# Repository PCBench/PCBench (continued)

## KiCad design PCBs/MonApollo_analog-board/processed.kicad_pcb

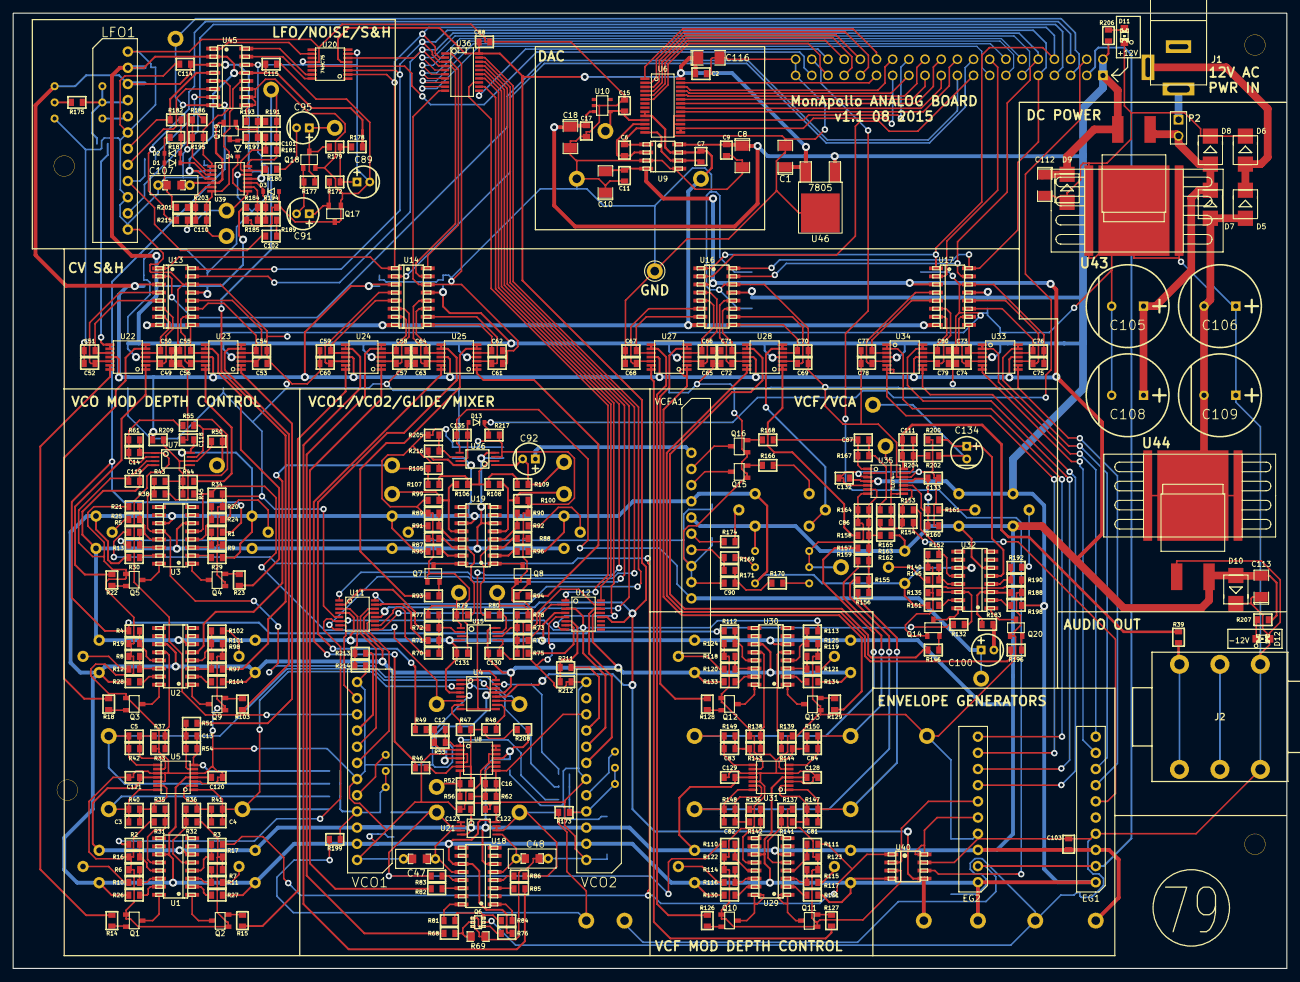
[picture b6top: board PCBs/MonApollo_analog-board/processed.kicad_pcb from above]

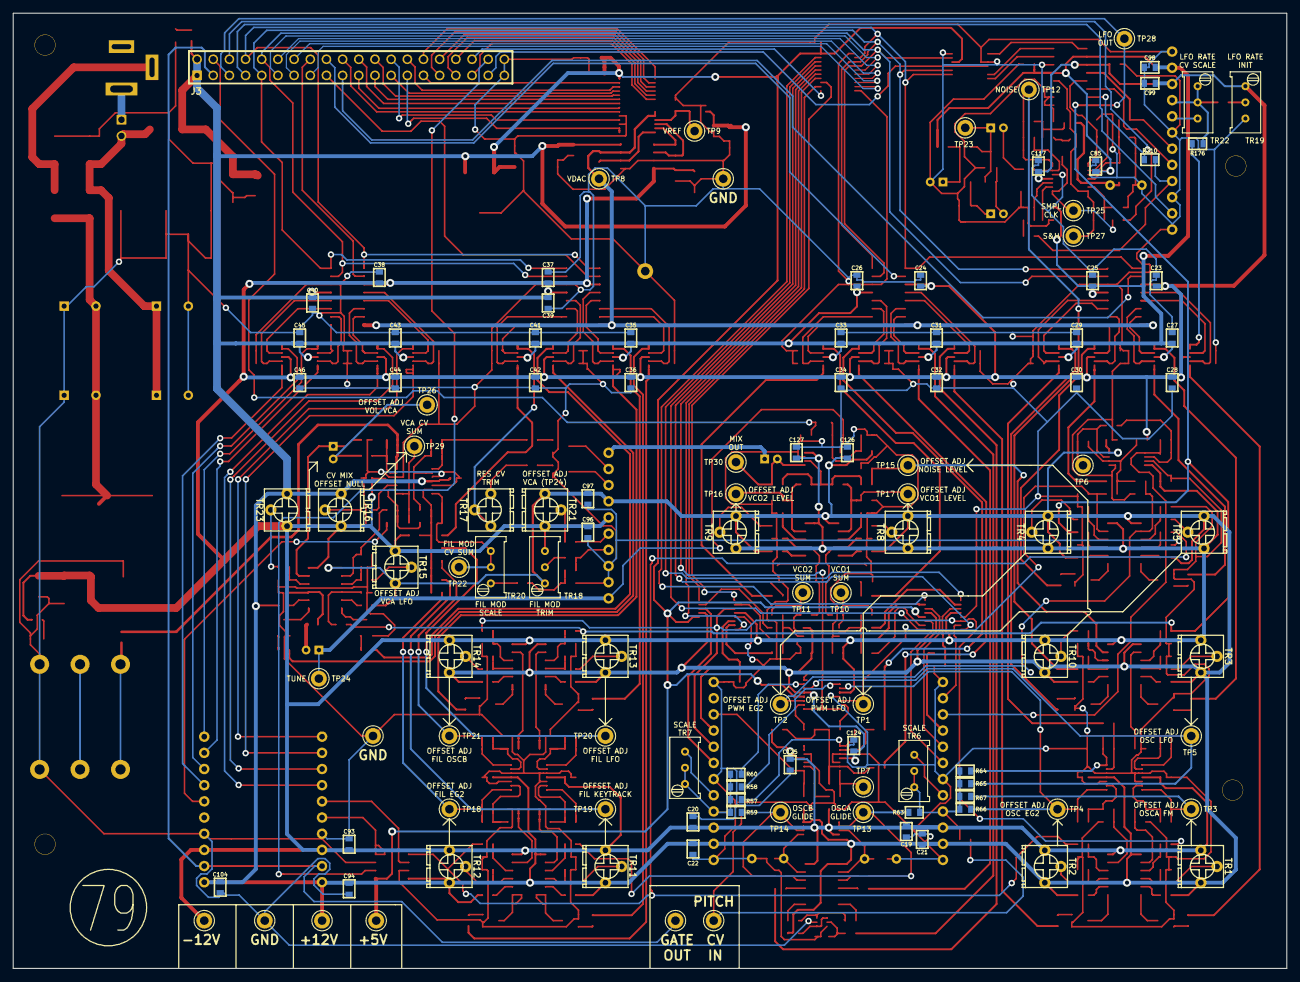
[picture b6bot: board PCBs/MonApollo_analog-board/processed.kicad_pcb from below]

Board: 2 copper layers, 200.0 x 150.0 mm, 506 parts (115 on the bottom side), 352 nets.

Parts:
C1, C8, C10, C18: 1µ; SMD-1206_Pol
C2, C9, C11, C15, C17, C23, C24, C25, C26, C27, C28, C29, C30, C31, C32, C33, C34, C35, C36, C37, C38, C39, C40, C41, C42, C43, C44, C45, C46, C85, C88, C114, C115, C117, C118, C119, C120, C121, C122, C123, C124, C125, C126, C127, C128, C129, C130, C131, C132, C133: 0.1µ; SM0603-C-JRL
C3, C4, C5, C12, C13, C14, C16, C81, C82, C83, C84, C86, C87, C101, C135: 10p; SM0603-C-JRL
C6, C7: 5.6p; SM0603-C-JRL
C19, C20, C21, C22, C93, C94, C96, C97, C98, C99, C103, C104: 1µ; SM0603-C-JRL
C47, C48: 470n; CAP-5MM-BOX-0805-COMBO
C49, C50, C51, C52, C53, C54, C55, C56, C57, C58, C59, C60, C61, C62, C63, C64, C65, C66, C67, C68, C69, C70, C71, C72, C73, C74, C75, C76, C77, C78, C79, C80: 0.01µ; SM0603-C-JRL
C89, C91: 47μ; 2MM-POL-CAP
C90: 100n; SM0603-C-JRL
C92: 1µ; 2MM-POL-CAP
C95: 10μ; 2MM-POL-CAP
C100, C134: 22µ; 2MM-POL-CAP
C102: 4.7n; SM0603-C-JRL
C105, C106, C108, C109: 1000µ; 5MM-POL-CAP
C107: 100n; CAP-5MM-BOX-0805-COMBO
C110: 1.5n; SM0603-C-JRL
C111: 100pF; SM0603-C-JRL
C112, C113, C116: 2.2µ; SMD-1206_Pol
D1, D2, D3, D4: DIODE; SOD323-JRL
D5, D6, D7, D8, D9, D10: DIODE; SMB
D11, D12: LED; LED-0805-JRL
D13: 1N4148; SOD323-JRL
EG1, EG2: EG
HOLE-0.125-INCH, HOLE-0.125-INCH_2, HOLE-0.125-INCH_3, HOLE-0.125-INCH_4: VAL**; HOLE-0.125-INCH
J1: AC IN; 2.1-MM-DC-EJ508A
J2: OUT; JACK_6.35_STEREO_TAYDA
J3: CONN_20X2; PIN_ARRAY_20X2
LFO1: VCO; VCO-SIP
P2: CONN_01X02; PIN_ARRAY_2X1
Q1, Q2, Q3, Q4, Q5, Q7, Q8, Q9, Q10, Q11, Q12, Q13, Q14, Q15, Q16, Q20: 2N3906; SOT23-JRL
Q6: BCM857BS; SOT363-JRL
Q17, Q18: NPN; SOT23-JRL
Q19: J111; SOT23-JRL
R1, R2, R3, R4, R5, R26, R27, R28, R29, R30, R79, R80, R95, R96, R97, R104, R110, R111, R112, R113, R130, R131, R132, R133, R134, R151, R183, R198: 12K; SM0603-R-JRL
R6, R7, R8, R9, R13, R16, R17, R19, R20, R21, R87, R88, R89, R90, R98, R101, R114, R115, R118, R119, R122, R123, R124, R125, R135, R140, R188, R190: 510; SM0603-R-JRL
R10, R11, R12, R24, R25, R91, R92, R102, R116, R117, R120, R121, R145, R174, R192: 2.2M; SM0603-R-JRL
R14, R15, R18, R126, R127, R128, R129: 68K; SM0603-R-JRL
R22, R23, R93, R94, R103, R146, R170, R171, R187, R195, R196: 18K; SM0603-R-JRL
R31, R32, R33, R34, R38, R99, R100, R105, R136, R137, R138, R139, R152, R172, R200: 47K; SM0603-R-JRL
R35, R36, R37, R141, R142, R143, R144: 91K; SM0603-R-JRL
R39, R189, R193, R206, R207: 1K; SM0603-R-JRL
R40, R41, R42, R147, R148, R149, R150, R216: 270K; SM0603-R-JRL
R43, R44, R45, R46, R47, R48, R49, R50, R51, R52, R53, R54, R55, R56, R57, R58, R59, R60, R61, R62, R63, R64, R65, R66, R67, R70, R71, R72, R73, R74, R75, R77, R78, R81, R84, R106, R107, R108, R109, R153, R154, R155, R156, R157, R158, R159, R163, R164, R165, R167, R173, R175, R176, R184, R199, R202, R204: 100K; SM0603-R-JRL
R68: 33K; SM0603-R-JRL
R69: 1K 3300ppm/K; SM0805-HAND
R76: 39K; SM0603-R-JRL
R82, R83, R85, R86: 4.7K; SM0603-R-JRL
R160, R179, R185, R191, R201, R205, R211, R213: 10K; SM0603-R-JRL
R161: 3.3M; SM0603-R-JRL
R162: 390K; SM0603-R-JRL
R166, R168: 27K; SM0603-R-JRL
R169: 680K**; SM0603-R-JRL
R177: 150K; SM0603-R-JRL
R178: 22; SM0603-R-JRL
R180: 15K; SM0603-R-JRL
R181, R203: 470K; SM0603-R-JRL
R182: 120K; SM0603-R-JRL
R186: 1.5K; SM0603-R-JRL
R194: 20K; SM0603-R-JRL
R197: 2.2meg; SM0603-R-JRL
R208, R209: 220K; SM0603-R-JRL
R210: 3.3K; SM0603-R-JRL
R212, R214: 9.1K; SM0603-R-JRL
R215: 10K; SM0603-JRL
R217: 22K; SM0603-R-JRL
TP1, TP2, TP3, TP4, TP5, TP6, TP7, TP8, TP9, TP10, TP11, TP12, TP13, TP14, TP15, TP16, TP17, TP18, TP19, TP20, TP21, TP22, TP23, TP24, TP25, TP26, TP27, TP28, TP29, TP30, TP31, TP32, TP33, TP34, TP35, TP36, TP37, TP38, TP39: CONN_1; TEST POINT
TR1, TR2, TR3, TR4, TR5, TR8, TR9, TR10, TR11, TR12, TR13, TR14, TR15, TR16, TR21, TR23: 100K; Bourns_3362P
TR6, TR7, TR20, TR22: 20K; Bourns-3296W
TR17: 20K; Bourns_3362P
TR18, TR19: 100K; Bourns-3296W
U1, U2, U3, U18, U19, U29, U30, U32: LM13700; SO16-JRL
U4, U11, U12: DG212B; TSSOP-16
U5, U8, U22, U23, U24, U25, U27, U28, U31, U33, U34, U35, U39: TL074-; tssop-14
U6: AD5556; TSSOP-28
U7, U15, U21, U26: TL072-; TSSOP8-JRL
U9: AD8672; SOIC-8-JRL
U10: ADR01; SOT-23-5
U13, U14, U16, U17, U45: DG408; SO16-JRL
U20: 74HC75; tssop-16
U36: 74LV573; SSOP-20
U38, U41: 0 - 10V; system79-logo-12mm
U40: DG419; SOIC-8-JRL
U42: 10 - 0V; system79-logo-12mm
U43: LM7812; D2-PAK-5733-HEAT-SINK
U44: LM7912; D2-PAK-5733-HEAT-SINK
U46: 7805; DPAK-2
VCFA1: VCF_VCA; VCF-VCA
VCO1, VCO2: VCO; VCO-SIP

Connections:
+5V: C1.1, C2.1, C88.1, C116.1, TP35.1, U4.12, U6.28, U11.12, U12.12, U20.5, U36.20, U40.5, U46.3
+12V: C8.1, C9.1, C17.1, C18.1, C21.1, C22.1, C25.1, C26.1, C27.1, C29.1, C31.1, C33.1, C35.1, C39.1, C40.1, C41.1, C43.1, C45.1, C85.1, C94.1, C97.1, C98.1, C104.1, C112.1, C115.1, C118.1, C120.1, C122.1, C124.1, C126.1, C128.1, C130.1, C132.1, D9.2, EG1.1, EG2.1, J3.1, J3.2, LFO1.2, R26.2, R27.2, R28.2, R29.2, R30.2, R76.2, R95.2, R96.2, R104.2, R130.2, R131.2, R133.2, R134.2, R151.2, R178.1, R184.1, R198.2, R206.1, R216.2, TP33.1, TR1.3, TR2.3, TR3.3, TR4.3, TR5.3, TR8.3, TR9.3, TR10.3, TR11.3, TR12.3, TR13.3, TR14.3, TR15.3, TR16.3, TR18.1, TR21.1, TR23.3, U1.11, U2.11, U3.11, U4.13, U5.4, U7.8, U8.4, U9.8, U10.3, U11.13, U12.13, U13.13, U14.13, U15.8, U16.13, U17.13, U18.11, U19.11, U21.8, U22.4, U23.4, U24.4, U25.4, U26.8, U27.4, U28.4, U29.11, U30.11, U31.4, U32.11, U33.4, U34.4, U35.4, U39.4, U40.4, U43.3, U45.2, U45.13, U46.1, VCFA1.4, VCO1.2, VCO2.2
-12V: C10.2, C11.2, C19.1, C20.1, C23.1, C24.1, C28.2, C30.2, C32.2, C34.2, C36.2, C37.1, C38.1, C42.2, C44.2, C46.2, C93.1, C96.1, C99.1, C103.1, C113.2, C114.1, C117.2, C119.2, C121.2, C123.2, C125.2, C127.2, C129.2, C131.2, C133.2, D10.1, EG1.3, EG2.3, LFO1.3, R162.2, R207.2, R208.1, R209.1, TP34.1, TR1.1, TR2.1, TR3.1, TR4.1, TR5.1, TR8.1, TR9.1, TR10.1, TR11.1, TR12.1, TR13.1, TR14.1, TR15.1, TR16.1, TR18.3, TR19.1, TR21.3, TR23.1, U1.6, U2.6, U3.6, U4.4, U5.11, U7.4, U8.11, U9.4, U11.4, U12.4, U13.3, U14.3, U15.4, U16.3, U17.3, U18.6, U19.6, U21.4, U22.11, U23.11, U24.11, U25.11, U26.4, U27.11, U28.11, U29.6, U30.6, U31.11, U32.6, U33.11, U34.11, U35.11, U39.11, U44.3, U45.3, VCFA1.5, VCO1.3, VCO2.3
/DAC0: J3.35, U6.6
/DAC1: J3.34, U6.5
/DAC2: J3.33, U6.4
/DAC3: J3.32, U6.3
/DAC4: J3.31, U6.2
/DAC5: J3.30, U6.1
/DAC6: J3.29, U6.27
/DAC7: J3.28, U6.26
/DAC8: J3.25, U6.25
/DAC9: J3.24, U6.24
/DAC10: J3.23, U6.23
/DAC11: J3.22, U6.22
/DAC12: J3.21, U6.21
/DAC13: J3.20, U6.20
/VREF: C15.1, TP9.1, U6.11, U10.4
AMP LFO AMT CV: R146.1, U28.8, U28.9
ANALOG SW LATCH: J3.36, U36.11
CUTOFF CV: R158.2, U28.1, U28.2
DAC MUX EN0: J3.19, U13.2
DAC MUX EN1: J3.18, U14.2
DAC MUX EN2: J3.17, U16.2
DAC MUX EN3: J3.16, U17.2
DB0: J3.8, U13.1, U14.1, U16.1, U17.1, U20.2, U36.2
DB1: J3.9, U13.16, U14.16, U16.16, U17.16, U20.3, U36.3
DB2: J3.10, U13.15, U14.15, U16.15, U17.15, U20.6, U36.4
DB3: J3.11, U36.5
DB4: J3.12, U36.6
DB5: J3.13, U36.7
DB6: J3.14, U36.8
DB7: J3.15, U36.9
EG1: EG1.6, R154.2
EG1 ATT CV: EG1.10, U33.1, U33.2
EG1 DEC CV: EG1.9, U33.6, U33.7
EG1 REL CV: EG1.8, U33.13, U33.14
EG1 SUS CV: EG1.7, U33.8, U33.9
EG2: R3.1, R5.1, R111.1, U40.1
EG2 ATT CV: EG2.10, U34.1, U34.2
EG2 DEC CV: EG2.9, U34.6, U34.7
EG2 POL: J3.38, U40.6
EG2 REL CV: EG2.8, U34.13, U34.14
EG2 SUS CV: EG2.7, U34.8, U34.9
EXT_CV_IN: R173.2, R199.2, TP38.1
FIL EG2 AMT CV: R127.1, U27.13, U27.14
FIL LFO AMT CV: R128.1, U27.6, U27.7
FIL OSCB AMT CV: R129.1, U27.1, U27.2
GATE: EG1.2, EG2.2, J3.3, TP39.1
GLIDE AMT CV: R68.2, U24.6, U24.7
GND: C1.2, C2.2, C8.2, C9.2, C10.1, C11.1, C15.2, C17.2, C18.2, C19.2, C20.2, C21.2, C22.2, C23.2, C24.2, C25.2, C26.2, C27.2, C28.1, C29.2, C30.1, C31.2, C32.1, C33.2, C34.1, C35.2, C36.1, C37.2, C38.2, C39.2, C40.2, C41.2, C42.1, C43.2, C44.1, C45.2, C46.1, C47.2, C48.2, C49.2, C50.2, C51.2, C52.2, C53.2, C54.2, C55.2, C56.2, C57.2, C58.2, C59.2, C60.2, C61.2, C62.2, C63.2, C64.2, C65.2, C66.2, C67.2, C68.2, C69.2, C70.2, C71.2, C72.2, C73.2, C74.2, C75.2, C76.2, C77.2, C78.2, C79.2, C80.2, C85.2, C88.2, C89.2, C90.2, C93.2, C94.2, C96.2, C97.2, C98.2, C99.2, C103.2, C104.2, C105.2, C106.1, C107.2, C108.2, C109.1, C112.2, C113.1, C114.2, C115.2, C116.2, C117.1, C118.2, C119.1, C120.2, C121.1, C122.2, C123.1, C124.2, C125.1, C126.2, C127.1, C128.2, C129.1, C130.2, C131.1, C132.2, C133.1, D1.2, D2.1, D3.1, D6.2, D8.2, D9.1, D10.2, D11.2, D12.1, EG1.4, EG2.4, J2.1, J3.39, J3.40, LFO1.1, LFO1.6, LFO1.10, LFO1.12, Q1.2, Q2.2, Q3.2, Q4.2, Q5.2, Q6.2, Q6.6, Q7.2, Q8.2, Q9.2, Q10.2, Q11.2, Q12.2, Q13.2, Q14.2, Q15.2, Q16.2, Q17.2, Q17.3, Q18.1, Q20.2, R6.1, R7.1, R8.1, R9.1, R13.1, R16.1, R17.1, R19.1, R20.1, R21.1, R31.1, R32.1, R33.1, R34.1, R38.1, R69.2, R87.1, R88.1, R89.1, R90.1, R98.1, R99.1, R100.1, R101.1, R105.1, R114.1, R115.1, R118.1, R119.1, R122.1, R123.1, R124.1, R125.1, R135.1, R136.1, R137.1, R138.1, R139.1, R140.1, R152.1, R160.1, R185.2, R186.2, R187.2, R188.1, R190.1, R193.2, R194.2, R200.1, R201.2, R205.2, R212.1, R214.1, R217.1, TP31.1, TP32.1, TP36.1, TP37.1, TR19.3, U4.5, U5.3, U5.5, U5.10, U5.12, U6.17, U6.19, U7.3, U7.5, U8.3, U8.5, U8.10, U8.12, U9.3, U9.5, U10.2, U11.5, U12.5, U13.14, U14.14, U15.3, U15.5, U16.14, U17.14, U20.7, U20.12, U26.3, U31.3, U31.5, U31.10, U31.12, U35.3, U35.5, U35.12, U36.1, U36.10, U39.12, U40.3, U40.7, U43.2, U44.1, U45.9, U45.10, U45.11, U45.14, U46.2, VCFA1.8, VCFA1.9, VCO1.1, VCO1.6, VCO1.12, VCO2.1, VCO2.6, VCO2.12
KEYTRACK AMT CV: R126.1, U27.8, U27.9
LFO: J3.5, R1.1, R4.1, R112.1, R132.1, TP28.1, U45.8
LFO DMUX EN: J3.37, U20.4, U20.13
LFO RATE CV: R176.2, U22.8, U22.9
LFO RESET: J3.7, LFO1.11
LFO TUNE: J3.6, R215.1
NOISE: C101.2, R97.1, R181.1, R191.2, TP12.1, U39.14
NOISE MIX CV: R103.1, U23.6, U23.7
unnamed: C3.1, R35.1, R40.2, U5.13
unnamed: C3.2, R40.1, R67.1, TP3.1, U5.14
unnamed: C4.1, R36.1, R41.2, U5.2
unnamed: C5.1, R37.1, R42.2, U5.9
unnamed: C6.1, U6.13, U9.1
unnamed: C6.2, U6.12, U9.2
unnamed: C7.2, U6.14, U9.6
unnamed: C12.1, R49.1, R53.2, U8.2
unnamed: C12.2, R53.1, R57.2, U8.1
unnamed: C13.1, R51.1, R54.1, U5.6
unnamed: C13.2, R54.2, R64.1, U5.7
unnamed: C14.1, R55.1, R61.2, U7.2
unnamed: C14.2, R61.1, U7.1, VCO1.10
unnamed: C16.1, R56.1, R62.2, U8.9
unnamed: C16.2, R62.1, U8.8, VCO2.10
unnamed: C47.1, U18.12, U21.3
unnamed: C48.1, U18.5, U21.5
unnamed: C81.1, R141.1, R147.2, U31.2
unnamed: C81.2, R147.1, R156.2, TP18.1, U31.1
unnamed: C82.1, R142.1, R148.2, U31.13
unnamed: C82.2, R148.1, R155.2, TP19.1, U31.14
unnamed: C83.1, R143.1, R149.2, U31.9
unnamed: C83.2, R149.1, R157.2, TP20.1, U31.8
unnamed: C84.1, R144.1, R150.2, U31.6
unnamed: C84.2, R150.1, R159.2, TP21.1, U31.7
unnamed: C86.1, R155.1, R156.1, R157.1, R158.1, R159.1, R162.1, R164.2, U35.6
unnamed: C86.2, R164.1, TP22.1, TR20.2, TR20.3, U35.7
unnamed: C87.1, R165.1, R167.2, U35.2
unnamed: C87.2, R167.1, R168.2, U35.1
unnamed: C89.1, R172.1, R178.2, R179.1
unnamed: C90.1, R170.1, R171.2
unnamed: C91.1, Q17.1, R172.2
unnamed: C91.2, Q18.2, R177.2
unnamed: C92.1, VCFA1.1
unnamed: C92.2, R109.2, TP30.1, U26.1
unnamed: C95.1, Q18.3, R177.1, R179.2, TP23.1
unnamed: C95.2, R180.2
unnamed: C100.1, C135.1, TP24.1, U26.5, VCFA1.10
unnamed: C100.2, R183.1
unnamed: C101.1, R180.1, R181.2, U39.13
unnamed: C102.1, LFO1.9, R210.2
unnamed: C102.2, R189.1
unnamed: C105.1, C108.1, D7.2, D8.1, P2.2, U43.1
unnamed: C106.2, C109.2, D5.1, D7.1, U44.2
unnamed: C107.1, Q19.1, U39.5
unnamed: C110.1, R201.1, R203.2, U39.6
unnamed: C110.2, R203.1, TP27.1, U39.7, U45.12
unnamed: C111.1, R202.2, R204.1, U35.13
unnamed: C111.2, R39.1, R204.2, U35.14
unnamed: C134.1, R200.2, U32.5
unnamed: C134.2, R202.1, TP26.1
unnamed: C135.2, D13.1, U26.7
unnamed: D1.1, D2.2, R182.1, R187.1, U39.3
unnamed: D3.2, R189.2, R194.1, U39.10
unnamed: D4.1, Q19.3, R197.2
unnamed: D4.2, R215.2, TP25.1, U39.8
unnamed: D5.2, D6.1, J1.3
unnamed: D11.1, R206.2
unnamed: D12.2, R207.1
unnamed: EG2.5, U40.8
unnamed: EG2.6, U40.2
unnamed: J1.1, P2.1
unnamed: J2.3, R39.2
unnamed: LFO1.4, R175.1, R176.1, TR22.1, TR22.2
unnamed: LFO1.5, TR22.3
unnamed: LFO1.7, R182.2, U45.4
unnamed: LFO1.8, U45.6
unnamed: Q1.1, R14.2
unnamed: Q1.3, U1.16
unnamed: Q2.1, R15.2
unnamed: Q2.3, U1.1
unnamed: Q3.1, R18.2
unnamed: Q3.3, U2.16
unnamed: Q4.1, R23.2
unnamed: Q4.3, U3.1
unnamed: Q5.1, R22.2
unnamed: Q5.3, U3.16
unnamed: Q6.1, Q6.4, R76.1
unnamed: Q6.3, R81.2, R84.2
unnamed: Q6.5, R68.1, R69.1
unnamed: Q7.1, R93.2
unnamed: Q7.3, U19.16
unnamed: Q8.1, R94.2
unnamed: Q8.3, U19.1
unnamed: Q9.1, R103.2
unnamed: Q9.3, U2.1
unnamed: Q10.1, R126.2
unnamed: Q10.3, U29.16
unnamed: Q11.1, R127.2
unnamed: Q11.3, U29.1
unnamed: Q12.1, R128.2
unnamed: Q12.3, U30.16
unnamed: Q13.1, R129.2
unnamed: Q13.3, U30.1
unnamed: Q14.1, R146.2
unnamed: Q14.3, U32.16
unnamed: Q15.1, R166.1
unnamed: Q15.3, VCFA1.3
unnamed: Q16.1, R168.1
unnamed: Q16.3, VCFA1.2
unnamed: Q19.2, R191.1, R193.1, R197.1
unnamed: Q20.1, R196.2
unnamed: Q20.3, U32.1
unnamed: R1.2, R9.2, U3.3
unnamed: R6.2, R10.1, U1.14
unnamed: R10.2, TR1.2
unnamed: R7.2, R11.1, U1.3
unnamed: R11.2, TR2.2
unnamed: R8.2, R12.1, U2.14
unnamed: R12.2, TR3.2
unnamed: R5.2, R13.2, U3.14
unnamed: R2.2, R16.2, U1.13
unnamed: R3.2, R17.2, U1.4
unnamed: R4.2, R19.2, U2.13
unnamed: R20.2, R24.2, U3.4
unnamed: R21.2, R25.2, U3.13
unnamed: R24.1, TR4.2
unnamed: R25.1, TR5.2
unnamed: R26.1, U1.15
unnamed: R27.1, U1.2
unnamed: R28.1, U2.15
unnamed: R29.1, U3.2
unnamed: R30.1, U3.15
unnamed: R31.2, R35.2, U1.12
unnamed: R32.2, R36.2, U1.5
unnamed: R33.2, R37.2, U2.12
unnamed: R47.2, U4.7
unnamed: R48.2, U4.10
unnamed: R50.1, R55.2, TP6.1, U7.7
unnamed: R52.1, R56.2, TP7.1, U8.7
unnamed: R58.2, U4.2
unnamed: R60.2, U4.15
unnamed: R70.1, R71.1, R72.1, R77.2, U15.2
unnamed: R70.2, U11.10
unnamed: R71.2, U11.15
unnamed: R72.2, U11.2
unnamed: R73.1, R74.1, R75.1, R78.2, U15.6
unnamed: R73.2, U12.15
unnamed: R74.2, U12.2
unnamed: R75.2, U12.7
unnamed: R77.1, R79.1, TP10.1, U15.1
unnamed: R78.1, R80.1, TP11.1, U15.7
unnamed: R79.2, R87.2, U19.14
unnamed: R80.2, R88.2, U19.3
unnamed: R81.1, U18.16
unnamed: R82.2, U18.14
unnamed: R83.2, U18.13
unnamed: R84.1, U18.1
unnamed: R85.2, U18.3
unnamed: R86.2, U18.4
unnamed: R89.2, R91.2, U19.13
unnamed: R90.2, R92.2, U19.4
unnamed: R91.1, TR8.2
unnamed: R92.1, TR9.2
unnamed: R95.1, U19.15
unnamed: R96.1, U19.2
unnamed: R97.2, R98.2, U2.3
unnamed: R100.2, R108.1, TP16.1, U19.5
unnamed: R101.2, R102.2, U2.4
unnamed: R102.1, TR10.2
unnamed: R104.1, U2.2
unnamed: R105.2, R107.1, TP15.1, U2.5
unnamed: R99.2, R106.1, TP17.1, U19.12
unnamed: R106.2, R107.2, R108.2, R109.1, U26.2
unnamed: R110.2, R122.2, U29.13
unnamed: R111.2, R123.2, U29.4
unnamed: R112.2, R124.2, U30.13
unnamed: R113.2, R125.2, U30.4
unnamed: R114.2, R116.1, U29.14
unnamed: R115.2, R117.1, U29.3
unnamed: R116.2, TR11.2
unnamed: R117.2, TR12.2
unnamed: R118.2, R120.1, U30.14
unnamed: R119.2, R121.1, U30.3
unnamed: R120.2, TR13.2
unnamed: R121.2, TR14.2
unnamed: R130.1, U29.15
unnamed: R131.1, U29.2
unnamed: R132.2, R135.2, U32.14
unnamed: R133.1, U30.15
unnamed: R134.1, U30.2
unnamed: R136.2, R142.2, U29.12
unnamed: R137.2, R141.2, U29.5
unnamed: R138.2, R143.2, U30.12
unnamed: R139.2, R144.2, U30.5
unnamed: R140.2, R145.2, U32.13
unnamed: R145.1, TR15.2
unnamed: R151.1, U32.15
unnamed: R152.2, R153.2, U32.12
unnamed: R153.1, R154.1, R163.2, U35.9
unnamed: R160.2, R161.2, U35.10
unnamed: R161.1, TR16.2
unnamed: R163.1, R165.2, TP29.1, U35.8
unnamed: R166.2, TR17.3
unnamed: R169.1, R171.1, VCFA1.7
unnamed: R169.2, TR18.2
unnamed: R170.2, TR20.1
unnamed: R57.1, R58.1, R59.1, R60.1, R173.1, TR7.1, TR7.2, VCO2.4
unnamed: R174.1, VCFA1.6
unnamed: R174.2, TR21.2
unnamed: R175.2, TR19.2
unnamed: R183.2, R188.2, U32.3
unnamed: R184.2, R185.1, U39.9
unnamed: R186.1, R195.2, U39.2
unnamed: R190.2, R192.2, U32.4
unnamed: R192.1, TR23.2
unnamed: R195.1, U39.1, U45.5
unnamed: R198.1, U32.2
unnamed: R63.2, R64.2, R65.2, R66.2, R67.2, R199.1, TR6.1, TR6.2, VCO1.4
unnamed: R205.1, R216.1, U26.6
unnamed: R46.1, R47.1, R48.1, R52.2, R208.2, U8.6
unnamed: R43.1, R44.1, R45.1, R50.2, R209.2, U7.6
unnamed: R210.1, U45.7
unnamed: R211.1, R212.2, U12.6
unnamed: R211.2, VCO2.9
unnamed: R213.1, R214.2, U11.3
unnamed: R213.2, VCO1.9
unnamed: TR6.3, VCO1.5
unnamed: TR7.3, VCO2.5
unnamed: U8.13, U8.14
unnamed: U11.7, VCO1.11
unnamed: U11.11, VCO1.7
unnamed: U11.14, VCO1.8
unnamed: U12.14, VCO2.7
unnamed: U20.10, U45.1
unnamed: U20.15, U45.16
unnamed: U20.16, U45.15
OSC EG2 AMT CV: R15.1, U24.13, U24.14
OSC EG2 MOD: C4.2, R41.1, R66.1, TP4.1, U4.3, U5.1
OSC LFO AMT CV: R18.1, U22.6, U22.7
OSC LFO MOD: C5.2, R42.1, R65.1, TP5.1, U4.14, U5.8
OSC PWM EG2 MOD: R38.2, R43.2, TP2.1, U3.12, U4.11
OSC PWM LFO MOD: R34.2, R45.2, TP1.1, U3.5, U4.6
OSC SYNC: U11.8, U36.16
OSCA FM AMT CV: R14.1, U22.13, U22.14
OSCA GLIDE CV: R63.1, R83.1, R110.1, TP13.1, U21.1, U21.2
OSCA INIT CV: R51.2, U23.1, U23.2
OSCA MIX CV: R93.1, U25.6, U25.7
OSCA PITCH CV: R82.1, U24.1, U24.2
OSCA PULSE: U11.1, U36.18
OSCA SAW: U11.16, U36.19
OSCA TRI: U11.9, U36.17
OSCB GLIDE CV: R59.2, R86.1, TP14.1, U21.6, U21.7
OSCB INIT CV: R49.2, U25.8, U25.9
OSCB MIX CV: R94.1, U25.1, U25.2
OSCB MOD: U4.1, U4.8, U4.9, U4.16, U36.15
OSCB PITCH CV: R85.1, U24.8, U24.9
OSCB PULSE: U12.8, U36.14
OSCB SAW: U12.1, U36.13
OSCB SAW WAVE: R2.1, R113.1, U11.6, U12.3, VCO2.8
OSCB TRI: U12.16, U36.12
PWM A CV: R44.2, U23.13, U23.14
PWM A EG2 AMT CV: R22.1, U22.1, U22.2
PWM A LFO AMT CV: R23.1, U23.8, U23.9
PWM B CV: R46.2, U25.13, U25.14
RES CV: TR17.1, TR17.2, U28.6, U28.7
SH0: C52.1, U13.4, U22.12
SH1: C51.1, U13.5, U22.10
SH2: C49.1, U13.6, U22.3
SH3: C50.1, U13.7, U22.5
SH4: C53.1, U13.12, U23.3
SH5: C54.1, U13.11, U23.5
SH6: C56.1, U13.10, U23.12
SH7: C55.1, U13.9, U23.10
SH8: C60.1, U14.4, U24.12
SH9: C59.1, U14.5, U24.10
SH10: C57.1, U14.6, U24.3
SH11: C58.1, U14.7, U24.5
SH12: C63.1, U14.12, U25.12
SH13: C64.1, U14.11, U25.10
SH14: C61.1, U14.10, U25.3
SH15: C62.1, U14.9, U25.5
SH16: C65.1, U16.4, U27.3
SH17: C66.1, U16.5, U27.5
SH18: C68.1, U16.6, U27.12
SH19: C67.1, U16.7, U27.10
SH20: C72.1, U16.12, U28.12
SH21: C71.1, U16.11, U28.10
SH22: C69.1, U16.10, U28.3
SH23: C70.1, U16.9, U28.5
SH24: C78.1, U17.4, U34.5
SH25: C77.1, U17.5, U34.3
SH26: C79.1, U17.6, U34.10
SH27: C80.1, U17.7, U34.12
SH28: C75.1, U17.12, U33.10
SH29: C76.1, U17.11, U33.12
SH30: C74.1, U17.10, U33.5
SH31: C73.1, U17.9, U33.3
TUNE: D13.2, J3.4, R217.2
VDAC: C7.1, TP8.1, U6.9, U6.10, U9.7, U13.8, U14.8, U16.8, U17.8
VOL CV: R196.1, U28.13, U28.14
~DAC RS: J3.26, U6.18
~DAC WR: J3.27, U6.15, U6.16

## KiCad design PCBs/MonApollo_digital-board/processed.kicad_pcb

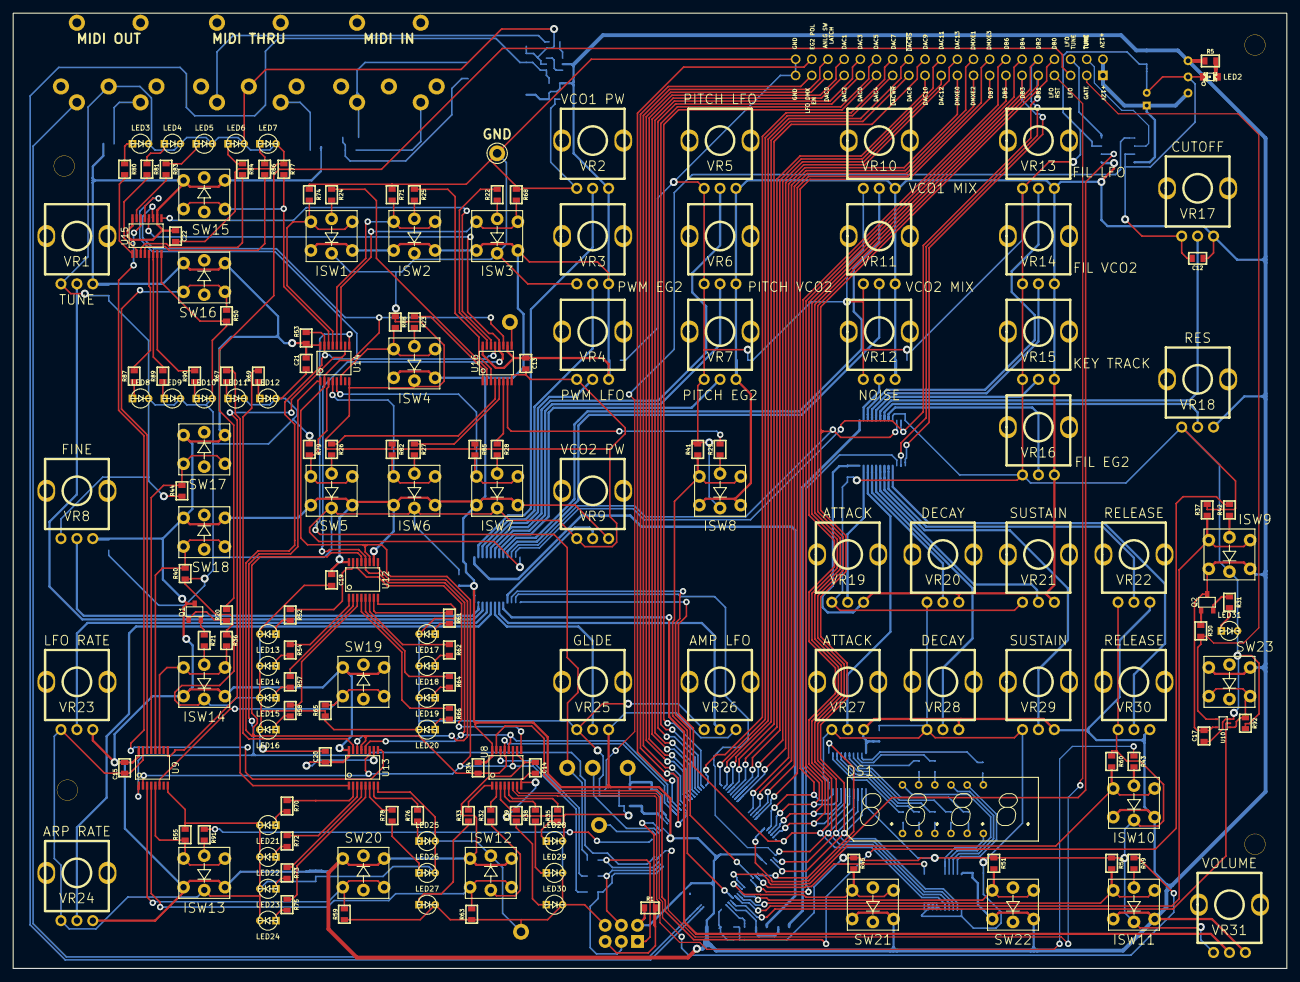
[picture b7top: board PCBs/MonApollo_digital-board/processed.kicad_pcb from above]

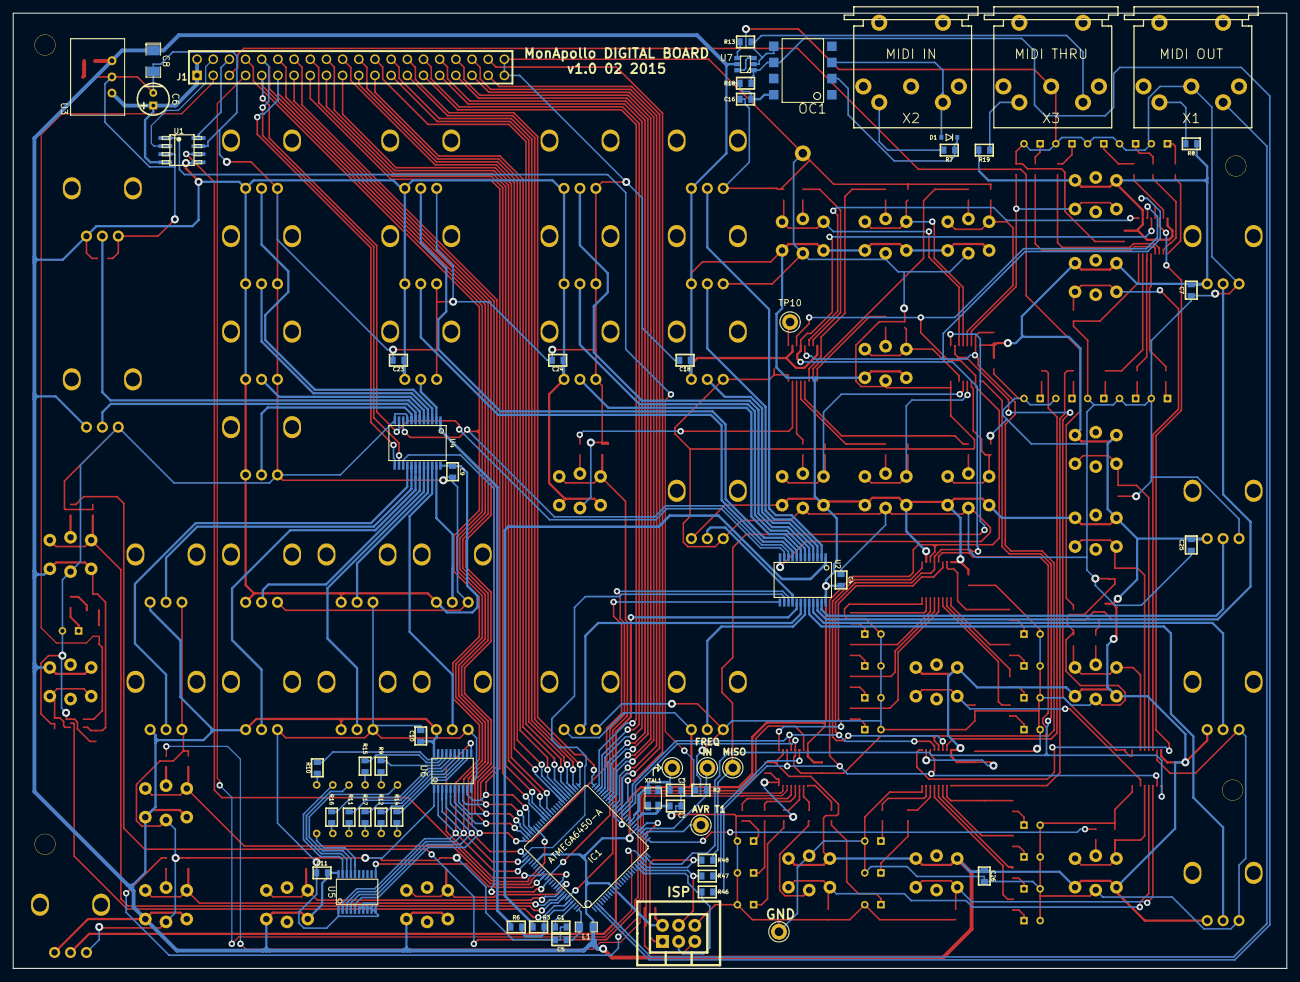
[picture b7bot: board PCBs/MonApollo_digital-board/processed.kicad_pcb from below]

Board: 2 copper layers, 200.0 x 150.0 mm, 240 parts (59 on the bottom side), 244 nets.

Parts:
C1, C4, C5, C7, C9, C10, C11, C12, C13, C14, C15, C16, C17, C18, C19, C20, C21, C22, C23, C24, C25, C26: 0.1µ; SM0603-C-JRL
C2, C3: 24p; SM0603-C-JRL
C6: 10µ; 2MM-POL-CAP
C8: 2.2µ; SMD-1206_Pol
D1: 1N4148; SOD323-JRL
DS1: LDQ-M286R1; LDQ-M286R1-DISPLAY
HOLE-0.125-INCH, HOLE-0.125-INCH_2, HOLE-0.125-INCH_3, HOLE-0.125-INCH_4: VAL**; HOLE-0.125-INCH
IC1: ATMEGA6450-A; TQFP-100
ISP1: CONN_3X2; CONN-2X3-0100R
ISW1, ISW2, ISW3, ISW4, ISW5, ISW6, ISW7, ISW8, ISW9, ISW10, ISW11, ISW12, ISW13, ISW14: TL1240
J1: CONN_20X2; PIN_ARRAY_20X2
L1: 10µH; SM0805-HAND
LED2: LED; LED-0805-JRL
LED3, LED4, LED5, LED6, LED7, LED8, LED9, LED10, LED11, LED12, LED13, LED14, LED15, LED16, LED17, LED18, LED19, LED20, LED21, LED22, LED23, LED24, LED25, LED26, LED27, LED28, LED29, LED30, LED31: LED; 3MM-LED
OC1: 6N137; 8-SMD
Q1, Q2: 2N3904; SOT23-JRL
R1: 100K; SM0603-R-JRL
R2, R3, R6, R21, R46, R47, R48: 1K; SM0603-R-JRL
R5, R31: 330; SM0603-R-JRL
R7, R8, R13, R19: 220; SM0603-R-JRL
R9, R22, R23, R24, R25, R26, R27, R28, R29, R32, R33, R35, R38, R39, R42, R43, R49, R52, R54, R57, R58, R61, R62, R64, R66, R67, R69, R70, R72, R73, R75, R76, R78, R80, R81, R83, R84, R86, R87, R89, R90, R91: 470; SM0603-R-JRL
R10, R11, R12, R14, R15, R16, R17: 560; SM0603-R-JRL
R18, R30, R34, R36, R37, R40, R41, R44, R45, R50, R51, R53, R55, R56, R59, R60, R63, R65, R68, R71, R74, R77, R79, R82, R85, R88, R92: 10K; SM0603-R-JRL
R20: 47K; SM0603-R-JRL
SW15, SW16, SW17, SW18, SW19, SW20, SW21, SW22, SW23: TACT_SWITCH; TL1240
TP1, TP2, TP9, TP10, TP11, TP12, TP13: CONN_1; TEST POINT
U1: DG419; SOIC-8-JRL
U2, U4: 74HC4067; SSOP24-JRL
U3: R-78E5.0-1.0; R-78E-0.5
U5, U6: 74LS573; TSSOP-20
U7: 74LVC2G04; SOT-23-6
U8, U12, U13, U15, U16: 74AC595; TSSOP-16
U9, U14: 74HC165; TSSOP-16
U10: 74LVC1G32; SOT-353
VR1: TUNE; RD901F-ALPHA-POT
VR2: VCO1 PW; RD901F-ALPHA-POT
VR3: PWM EG2; RD901F-ALPHA-POT
VR4: PWM LFO; RD901F-ALPHA-POT
VR5: PITCH LFO; RD901F-ALPHA-POT
VR6: PITCH VCO2; RD901F-ALPHA-POT
VR7: PITCH EG2; RD901F-ALPHA-POT
VR8: FINE; RD901F-ALPHA-POT
VR9: VCO2 PW; RD901F-ALPHA-POT
VR10: VCO1 MIX; RD901F-ALPHA-POT
VR11: VCO2 MIX; RD901F-ALPHA-POT
VR12: NOISE; RD901F-ALPHA-POT
VR13: FIL LFO; RD901F-ALPHA-POT
VR14: FIL VCO2; RD901F-ALPHA-POT
VR15: KEY TRACK; RD901F-ALPHA-POT
VR16: FIL EG2; RD901F-ALPHA-POT
VR17: CUTOFF; RD901F-ALPHA-POT
VR18: RES; RD901F-ALPHA-POT
VR19, VR27: ATTACK; RD901F-ALPHA-POT
VR20, VR28: DECAY; RD901F-ALPHA-POT
VR21, VR29: SUSTAIN; RD901F-ALPHA-POT
VR22, VR30: RELEASE; RD901F-ALPHA-POT
VR23: LFO RATE; RD901F-ALPHA-POT
VR24: ARP RATE; RD901F-ALPHA-POT
VR25: GLIDE; RD901F-ALPHA-POT
VR26: AMP LFO; RD901F-ALPHA-POT
VR31: VOLUME; RD901F-ALPHA-POT
X1: MIDI OUT; TEDIN-D501
X2: MIDI IN; TEDIN-D501
X3: MIDI THRU; TEDIN-D501
XTAL1: 20MHz; 403-XTAL-4-SMD

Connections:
+5V: C4.1, C7.1, C8.1, C9.1, C10.1, C11.1, C12.1, C13.1, C14.1, C15.1, C16.1, C17.1, C18.1, C19.1, C20.1, C21.1, C22.1, C23.1, C24.1, C25.1, C26.1, IC1.10, IC1.31, IC1.80, ISP1.2, ISW1.1, ISW2.1, ISW3.1, ISW4.1, ISW5.1, ISW6.1, ISW7.1, ISW8.1, ISW9.1, ISW10.1, ISW11.1, ISW12.1, ISW13.1, ISW14.1, L1.1, OC1.8, Q1.3, Q2.3, R1.1, R5.2, R8.1, R18.2, R19.1, R34.1, R53.1, SW15.1, SW16.1, SW17.1, SW18.1, SW19.1, SW20.1, SW21.1, SW22.1, SW23.2, U1.5, U2.24, U3.3, U4.24, U5.20, U6.20, U7.5, U8.10, U8.16, U9.16, U10.5, U12.10, U12.16, U13.10, U13.16, U14.16, U15.10, U15.16, U16.10, U16.16, VR1.3, VR2.3, VR3.3, VR4.3, VR5.3, VR6.3, VR7.3, VR8.3, VR9.3, VR10.3, VR11.3, VR12.3, VR13.3, VR14.3, VR15.3, VR16.3, VR17.3, VR18.3, VR19.3, VR20.3, VR21.3, VR22.3, VR23.3, VR24.3, VR25.3, VR26.3, VR27.3, VR28.3, VR29.3, VR30.3, VR31.3
+12V: C6.1, J1.1, J1.2, U1.4, U3.1
/DAC0: IC1.43, J1.35
/DAC1: IC1.44, J1.34
/DAC2: IC1.45, J1.33
/DAC3: IC1.46, J1.32
/DAC4: IC1.47, J1.31
/DAC5: IC1.48, J1.30
/DAC6: IC1.49, J1.29
/DAC7: IC1.50, J1.28
/DAC8: IC1.53, J1.25
/DAC9: IC1.54, J1.24
/DAC10: IC1.55, J1.23
/DAC11: IC1.56, J1.22
/DAC12: IC1.57, J1.21
/DAC13: IC1.58, J1.20
ANALOG SW LATCH: IC1.41, J1.36
ARP_SYNC: IC1.26, R91.2
DAC MUX EN0: IC1.63, J1.19
DAC MUX EN1: IC1.64, J1.18
DAC MUX EN2: IC1.65, J1.17
DAC MUX EN3: IC1.66, J1.16
DB0: IC1.78, J1.8, U2.10, U4.10, U5.2, U6.2
DB1: IC1.77, J1.9, U2.11, U4.11, U5.3, U6.3
DB2: IC1.76, J1.10, U2.14, U4.14, U5.4, U6.4
DB3: IC1.75, J1.11, U2.13, U4.13, U5.5, U6.5
DB4: IC1.74, J1.12, U6.6
DB5: IC1.73, J1.13, U6.7
DB6: IC1.72, J1.14, U6.8
DB7: IC1.71, J1.15, U6.9
DGATE: IC1.96, U10.2
DISP ANODE LATCH: IC1.85, U5.11
DISP CATHODE LATCH: IC1.84, U6.11
EG2 POL: IC1.39, J1.38
FREQ IN: IC1.29, R2.1, TP12.1
GATE: J1.3, R30.2, U10.4
GND: C1.2, C2.1, C3.1, C4.2, C5.2, C6.2, C7.2, C8.2, C9.2, C10.2, C11.2, C12.2, C13.2, C14.2, C15.2, C16.2, C17.2, C18.2, C19.2, C20.2, C21.2, C22.2, C23.2, C24.2, C25.2, C26.2, ISP1.6, ISW1.5, ISW2.5, ISW3.5, ISW4.5, ISW5.5, ISW6.5, ISW7.5, ISW8.5, ISW9.5, ISW10.5, ISW11.5, ISW12.5, ISW13.5, ISW14.5, J1.39, J1.40, LED2.2, LED3.2, LED4.2, LED5.2, LED6.2, LED7.2, LED8.2, LED9.2, LED10.2, LED11.2, LED12.2, LED13.2, LED14.2, LED15.2, LED16.2, LED17.2, LED18.2, LED19.2, LED20.2, LED21.2, LED22.2, LED23.2, LED24.2, LED25.2, LED26.2, LED27.2, LED28.2, LED29.2, LED30.2, LED31.2, OC1.5, R36.1, R37.1, R40.1, R41.1, R44.1, R45.1, R50.1, R51.1, R55.1, R56.1, R59.1, R60.1, R63.1, R65.1, R68.1, R71.1, R74.1, R77.1, R79.1, R82.1, R85.1, R88.1, R92.1, TP1.1, TP2.1, U1.3, U1.7, U2.12, U3.2, U4.9, U4.12, U5.1, U5.6, U5.7, U5.8, U5.9, U5.10, U6.1, U6.10, U7.2, U8.8, U9.8, U9.15, U10.3, U12.8, U13.8, U14.8, U15.8, U16.8, VR1.1, VR2.1, VR3.1, VR4.1, VR5.1, VR6.1, VR7.1, VR8.1, VR9.1, VR10.1, VR11.1, VR12.1, VR13.1, VR14.1, VR15.1, VR16.1, VR17.1, VR18.1, VR19.1, VR20.1, VR21.1, VR22.1, VR23.1, VR24.1, VR25.1, VR26.1, VR27.1, VR28.1, VR29.1, VR30.1, VR31.1, X1.2, X3.2
ISW8: IC1.95, ISW8.2, R41.2
ISW9: IC1.94, ISW9.2, R37.2
ISW10: IC1.90, ISW10.2, R60.2
ISW11: IC1.93, ISW11.2, R56.2
LED_LATCH: IC1.38, U8.12, U12.12, U13.12, U15.12, U16.12
LFO: J1.5, R20.2
LFO DMUX EN: IC1.40, J1.37
LFO RESET: IC1.23, J1.7
LFO TUNE: J1.6, U1.8
MISO: IC1.22, ISP1.1, R48.2
MOSI: IC1.21, ISP1.4, R47.2
unnamed: C1.1, IC1.98
unnamed: C2.2, IC1.33, XTAL1.2
unnamed: C3.2, IC1.34, TP11.1, XTAL1.1
unnamed: C5.1, IC1.100, L1.2
unnamed: D1.1, OC1.3, X2.5
unnamed: D1.2, OC1.2, R7.1
unnamed: DS1.1, R14.1
unnamed: DS1.2, R12.1
unnamed: DS1.3, R17.1
unnamed: DS1.4, R11.1
unnamed: DS1.5, R16.1
unnamed: DS1.6, U5.16
unnamed: DS1.7, R10.1
unnamed: DS1.8, U5.19
unnamed: DS1.9, U5.18
unnamed: DS1.10, R15.1
unnamed: DS1.11, R9.1
unnamed: DS1.12, U5.17
unnamed: IC1.28, TP13.1
unnamed: ISW1.2, R74.2, U14.13
unnamed: ISW1.6, R24.1
unnamed: ISW2.2, R71.2, U14.12
unnamed: ISW2.6, R25.1
unnamed: ISW3.2, R68.2, U14.11
unnamed: ISW3.6, R22.1
unnamed: ISW4.2, R88.2, U14.6
unnamed: ISW4.6, R23.1
unnamed: ISW5.2, R79.2, U14.3
unnamed: ISW5.6, R26.1
unnamed: ISW6.2, R82.2, U14.4
unnamed: ISW6.6, R27.1
unnamed: ISW7.2, R85.2, U14.5
unnamed: ISW7.6, R28.1
unnamed: ISW8.6, R29.1
unnamed: ISW9.6, R42.1
unnamed: ISW10.6, R43.1
unnamed: ISW11.6, R49.1
unnamed: ISW12.2, R63.2, U9.4
unnamed: ISW12.6, R32.1
unnamed: ISW13.2, R55.2, U9.5
unnamed: ISW13.6, R91.1
unnamed: ISW14.2, R36.2, U9.11
unnamed: ISW14.6, R21.2
unnamed: LED2.1, R5.1
unnamed: LED3.1, R80.1
unnamed: LED4.1, R81.1
unnamed: LED5.1, R83.1
unnamed: LED6.1, R84.1
unnamed: LED7.1, R86.1
unnamed: LED8.1, R87.1
unnamed: LED9.1, R89.1
unnamed: LED10.1, R90.1
unnamed: LED11.1, R67.1
unnamed: LED12.1, R69.1
unnamed: LED13.1, R52.1
unnamed: LED14.1, R54.1
unnamed: LED15.1, R57.1
unnamed: LED16.1, R58.1
unnamed: LED17.1, R61.1
unnamed: LED18.1, R62.1
unnamed: LED19.1, R64.1
unnamed: LED20.1, R66.1
unnamed: LED21.1, R70.1
unnamed: LED22.1, R72.1
unnamed: LED23.1, R73.1
unnamed: LED24.1, R75.1
unnamed: LED25.1, R76.1
unnamed: LED26.1, R78.1
unnamed: LED27.1, R33.1
unnamed: LED28.1, R35.1
unnamed: LED29.1, R38.1
unnamed: LED30.1, R39.1
unnamed: LED31.1, R31.2
unnamed: Q1.1, R21.1
unnamed: Q1.2, R20.1
unnamed: Q2.1, R31.1
unnamed: Q2.2, R30.1
unnamed: R2.2, U1.1
unnamed: R3.1, U2.1
unnamed: R6.1, U4.1
unnamed: R7.2, X2.4
unnamed: R8.2, X1.4
unnamed: R9.2, U6.17
unnamed: R10.2, U6.19
unnamed: R11.2, U6.15
unnamed: R12.2, U6.13
unnamed: R13.1, X3.5
unnamed: R13.2, U7.4
unnamed: R14.2, U6.12
unnamed: R15.2, U6.18
unnamed: R16.2, U6.16
unnamed: R17.2, U6.14
unnamed: R19.2, X3.4
unnamed: R22.2, U16.15
unnamed: R23.2, U16.1
unnamed: R24.2, U16.2
unnamed: R25.2, U16.3
unnamed: R26.2, U16.4
unnamed: R27.2, U16.5
unnamed: R28.2, U16.6
unnamed: R29.2, U16.7
unnamed: R32.2, U8.2
unnamed: R33.2, U8.1
unnamed: R35.2, U8.5
unnamed: R38.2, U8.4
unnamed: R39.2, U8.3
unnamed: R40.2, SW18.2, U9.12
unnamed: R42.2, U8.15
unnamed: R43.2, U8.6
unnamed: R44.2, SW17.2, U9.13
unnamed: R49.2, U8.7
unnamed: R50.2, SW16.2, U9.14
unnamed: R52.2, U12.15
unnamed: R54.2, U12.1
unnamed: R57.2, U12.2
unnamed: R58.2, U12.3
unnamed: R59.2, SW20.2, U9.3
unnamed: R61.2, U12.7
unnamed: R62.2, U12.6
unnamed: R64.2, U12.5
unnamed: R65.2, SW19.2, U9.6
unnamed: R66.2, U12.4
unnamed: R67.2, U13.1
unnamed: R69.2, U13.15
unnamed: R70.2, U13.2
unnamed: R72.2, U13.3
unnamed: R73.2, U13.4
unnamed: R75.2, U13.5
unnamed: R76.2, U13.7
unnamed: R77.2, SW15.2, U14.14
unnamed: R78.2, U13.6
unnamed: R80.2, U15.1
unnamed: R81.2, U15.2
unnamed: R83.2, U15.15
unnamed: R84.2, U15.3
unnamed: R86.2, U15.4
unnamed: R87.2, U15.5
unnamed: R89.2, U15.6
unnamed: R90.2, U15.7
unnamed: R92.2, SW23.1, U10.1
unnamed: TP10.1, U16.9
unnamed: U2.2, VR2.2
unnamed: U2.3, VR3.2
unnamed: U2.4, VR4.2
unnamed: U2.5, VR5.2
unnamed: U2.6, VR6.2
unnamed: U2.7, VR7.2
unnamed: U2.8, VR10.2
unnamed: U2.9, VR11.2
unnamed: U2.16, VR9.2
unnamed: U2.17, VR31.2
unnamed: U2.18, VR26.2
unnamed: U2.19, VR25.2
unnamed: U2.20, VR24.2
unnamed: U2.21, VR23.2
unnamed: U2.22, VR1.2
unnamed: U2.23, VR8.2
unnamed: U4.2, VR12.2
unnamed: U4.3, VR13.2
unnamed: U4.4, VR14.2
unnamed: U4.5, VR15.2
unnamed: U4.6, VR17.2
unnamed: U4.7, VR18.2
unnamed: U4.8, VR16.2
unnamed: U4.16, VR30.2
unnamed: U4.17, VR22.2
unnamed: U4.18, VR29.2
unnamed: U4.19, VR21.2
unnamed: U4.20, VR28.2
unnamed: U4.21, VR20.2
unnamed: U4.22, VR27.2
unnamed: U4.23, VR19.2
unnamed: U7.3, U7.6
unnamed: U12.9, U13.14
unnamed: U8.9, U12.14
unnamed: U13.9, U15.14
unnamed: U9.9, U14.10
unnamed: U15.9, U16.14
POTMUX: IC1.97, R3.2, R6.2
SCK: IC1.20, ISP1.3, R46.2
SPI_MISO: R48.1, TP9.1, U14.9
SPI_MOSI: R47.1, U8.14
SPI_SCK: R46.1, U8.11, U9.2, U12.11, U13.11, U14.2, U15.11, U16.11
SW21: IC1.91, R45.2, SW21.2
SW22: IC1.92, R51.2, SW22.2
SWITCH_LATCH: IC1.24, U9.1, U14.1
TUNE: J1.4, U1.2
TUNE SEL: IC1.70, U1.6
UART RX: IC1.2, OC1.6, R18.1, U7.1
UART TX: IC1.3, X1.5
~DAC RS: IC1.52, J1.26
~DAC WR: IC1.51, J1.27
~POTMUX EN0: IC1.86, U2.15
~POTMUX EN1: IC1.87, U4.15
~RESET: IC1.30, ISP1.5, R1.2
~SPI_EN: IC1.37, R34.2, R53.2, U8.13, U12.13, U13.13, U14.15, U15.13, U16.13
